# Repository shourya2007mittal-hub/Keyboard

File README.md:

# KEYBOARD
So I am making an 60% layout keyboard with 2 rotor encoders .So In total there will be 61 Keys and 2 rotor encoders for volume and britness controle but there aren't that many gpios in any devboard therefore I would be using keyboard matrix and diodes to restrict gosting and I choosed Raspberry Pico as controller because it supports KMK and have enought Gpios as well.I also added stabalizers for any keys whose size is over 1.75U
## Features

- Base on Raspberry pico
- Has 61 keys ( 60% Keyboard Matrix)
- Has 2 Rotor Encoder
  ### Schematic
  br>

  ###  PCB Design
<br>

### 3D Design

- ## Bill of Materials (BOM)

| # | Item | Description | Quantity | Unit Price (USD) | Total (USD) | Link |
|---|------|-------------|----------|------------------|-------------|------|
| 1 | 80Retros x HMX Volume | Mechanical switches (pack of 35) | 2 packs | 17.8 | 35.6 | https://stackskb.com/store/hmx-volume-0-pack-of-35/ |
| 2 | 1N4148 Diode | DO-35 switching diode | 61 | 0 | 0 | | Already have
| 3 | Raspberry Pi Pico H | RP2040 microcontroller board | 1 | 5.5 | 5.5 | https://robu.in/product/raspberry-pi-pico-with-headers/ |
| 4 |  Keycap Set | Full keycap set | 1 | 26.2 | 26.2 | https://stackskb.com/store/blue-and-blue-double-shot-abs-cherry-profile-keycaps-pre-order/
| 5 | Screw-In Stabilizers V2 | Keyboard stabilizers | 1 | 0 |0 | Already have |
| 6 | PCB  + Shipping | PCB fabrication (JLCPCB) | 1 |31.55| 31.55 | https://jlcpcb.com |

**Estimated Total Hardware Cost:** **USD 98.85**

## Hardware
- Raspberry Pico 
- Cherry MX compatible Switches
- Diode
- 2 layer PCB
- 2 Rotor Encoder

## Firmware
- It is Based on KMK and Circuit Python

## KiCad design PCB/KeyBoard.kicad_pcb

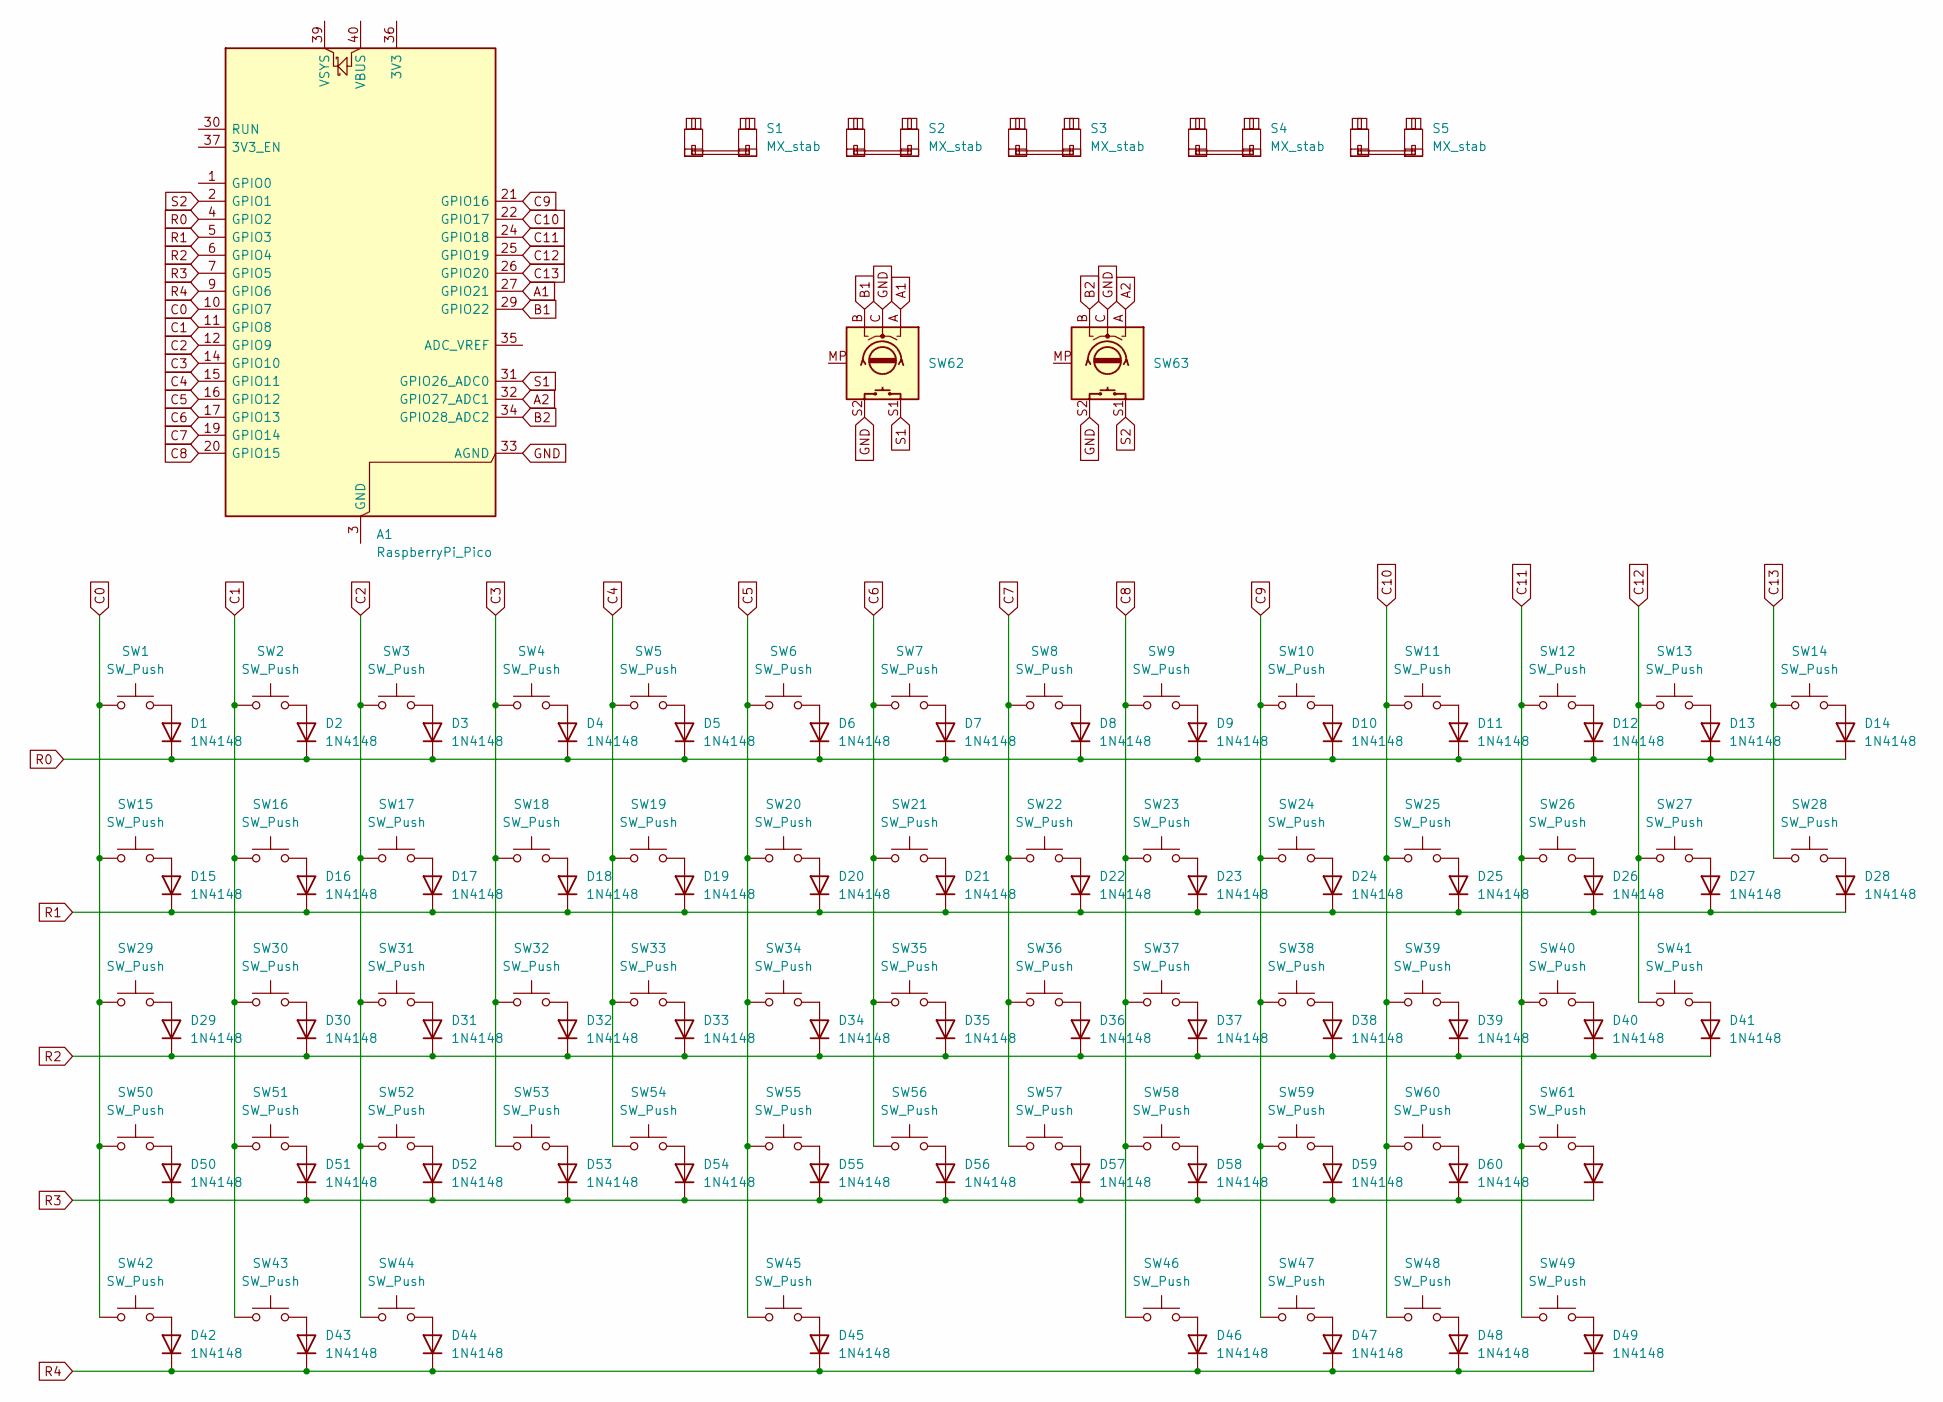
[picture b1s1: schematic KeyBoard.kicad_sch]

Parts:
A1: RaspberryPi_Pico; RaspberryPi_Pico_Common_Unspecified
D1, D2, D3, D4, D5, D6, D7, D8, D9, D10, D11, D12, D13, D14, D15, D16, D17, D18, D19, D20, D21, D22, D23, D24, D25, D26, D27, D28, D29, D30, D31, D32, D33, D34, D35, D36, D37, D38, D39, D40, D41, D42, D43, D44, D45, D46, D47, D48, D49, D50, D51, D52, D53, D54, D55, D56, D57, D58, D59, D60, D61: 1N4148; D_DO-35_SOD27_P7.62mm_Horizontal
S1: MX_stab; STAB_MX_2u
S2, S3: MX_stab; STAB_MX_2.25u
S4: MX_stab; STAB_MX_2.75u
S5: MX_stab; STAB_MX_6.25u
SW1, SW2, SW3, SW4, SW5, SW6, SW7, SW8, SW9, SW10, SW11, SW12, SW13, SW16, SW17, SW18, SW19, SW20, SW21, SW22, SW23, SW24, SW25, SW26, SW27, SW30, SW31, SW32, SW33, SW34, SW35, SW36, SW37, SW38, SW39, SW40, SW51, SW52, SW53, SW54, SW55, SW56, SW57, SW58, SW59, SW60: SW_Push; SW_Cherry_MX_1.00u_PCB
SW14: SW_Push; SW_Cherry_MX_2.00u_PCB
SW15: SW_Push; SW_Cherry_MX_1.50u_PCB
SW28: SW_Push; SW_Cherry_MX_1.50u_Plate
SW29: SW_Push; SW_Cherry_MX_1.75u_PCB
SW41, SW50: SW_Push; SW_Cherry_MX_2.25u_PCB
SW42, SW43, SW44, SW46, SW48, SW49: SW_Push; SW_Cherry_MX_1.25u_PCB
SW45: SW_Push; SW_Cherry_MX_6.25u_PCB
SW47: SW_Push; SW_Cherry_MX_1.25u_Plate
SW61: SW_Push; SW_Cherry_MX_2.75u_PCB
SW62, SW63: RotaryEncoder_Switch_MP; RotaryEncoder_Alps_EC11E-Switch_Vertical_H20mm

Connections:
A1: A1.27 (GPIO21), SW62.A
A2: A1.32 (GPIO27_ADC1), SW63.A
B1: A1.29 (GPIO22), SW62.B
B2: A1.34 (GPIO28_ADC2), SW63.B
C0: A1.10 (GPIO7), SW1.1, SW15.1, SW29.1, SW42.1, SW50.1
C1: A1.11 (GPIO8), SW2.1, SW16.1, SW30.1, SW43.1, SW51.1
C2: A1.12 (GPIO9), SW3.1, SW17.1, SW31.1, SW44.1, SW52.1
C3: A1.14 (GPIO10), SW4.1, SW18.1, SW32.1, SW53.1
C4: A1.15 (GPIO11), SW5.1, SW19.1, SW33.1, SW54.1
C5: A1.16 (GPIO12), SW6.1, SW20.1, SW34.1, SW45.1, SW55.1
C6: A1.17 (GPIO13), SW7.1, SW21.1, SW35.1, SW56.1
C7: A1.19 (GPIO14), SW8.1, SW22.1, SW36.1, SW57.1
C8: A1.20 (GPIO15), SW9.1, SW23.1, SW37.1, SW46.1, SW58.1
C9: A1.21 (GPIO16), SW10.1, SW24.1, SW38.1, SW47.1, SW59.1
C10: A1.22 (GPIO17), SW11.1, SW25.1, SW39.1, SW48.1, SW60.1
C11: A1.24 (GPIO18), SW12.1, SW26.1, SW40.1, SW49.1, SW61.1
C12: A1.25 (GPIO19), SW13.1, SW27.1, SW41.1
C13: A1.26 (GPIO20), SW14.1, SW28.1
GND: A1.33 (AGND), SW62.C, SW62.S2, SW63.C, SW63.S2
unnamed: A1.3 (GND), A1.8 (GND), A1.13 (GND), A1.18 (GND), A1.23 (GND), A1.28 (GND), A1.38 (GND)
unnamed: D1.2 (A), SW1.2
unnamed: D2.2 (A), SW2.2
unnamed: D3.2 (A), SW3.2
unnamed: D4.2 (A), SW4.2
unnamed: D5.2 (A), SW5.2
unnamed: D6.2 (A), SW6.2
unnamed: D7.2 (A), SW7.2
unnamed: D8.2 (A), SW8.2
unnamed: D9.2 (A), SW9.2
unnamed: D10.2 (A), SW10.2
unnamed: D11.2 (A), SW11.2
unnamed: D12.2 (A), SW12.2
unnamed: D13.2 (A), SW13.2
unnamed: D14.2 (A), SW14.2
unnamed: D15.2 (A), SW15.2
unnamed: D16.2 (A), SW16.2
unnamed: D17.2 (A), SW17.2
unnamed: D18.2 (A), SW18.2
unnamed: D19.2 (A), SW19.2
unnamed: D20.2 (A), SW20.2
unnamed: D21.2 (A), SW21.2
unnamed: D22.2 (A), SW22.2
unnamed: D23.2 (A), SW23.2
unnamed: D24.2 (A), SW24.2
unnamed: D25.2 (A), SW25.2
unnamed: D26.2 (A), SW26.2
unnamed: D27.2 (A), SW27.2
unnamed: D28.2 (A), SW28.2
unnamed: D29.2 (A), SW29.2
unnamed: D30.2 (A), SW30.2
unnamed: D31.2 (A), SW31.2
unnamed: D32.2 (A), SW32.2
unnamed: D33.2 (A), SW33.2
unnamed: D34.2 (A), SW34.2
unnamed: D35.2 (A), SW35.2
unnamed: D36.2 (A), SW36.2
unnamed: D37.2 (A), SW37.2
unnamed: D38.2 (A), SW38.2
unnamed: D39.2 (A), SW39.2
unnamed: D40.2 (A), SW40.2
unnamed: D41.2 (A), SW41.2
unnamed: D42.2 (A), SW42.2
unnamed: D43.2 (A), SW43.2
unnamed: D44.2 (A), SW44.2
unnamed: D45.2 (A), SW45.2
unnamed: D46.2 (A), SW46.2
unnamed: D47.2 (A), SW47.2
unnamed: D48.2 (A), SW48.2
unnamed: D49.2 (A), SW49.2
unnamed: D50.2 (A), SW50.2
unnamed: D51.2 (A), SW51.2
unnamed: D52.2 (A), SW52.2
unnamed: D53.2 (A), SW53.2
unnamed: D54.2 (A), SW54.2
unnamed: D55.2 (A), SW55.2
unnamed: D56.2 (A), SW56.2
unnamed: D57.2 (A), SW57.2
unnamed: D58.2 (A), SW58.2
unnamed: D59.2 (A), SW59.2
unnamed: D60.2 (A), SW60.2
unnamed: D61.2 (A), SW61.2
R0: A1.4 (GPIO2), D1.1 (K), D2.1 (K), D3.1 (K), D4.1 (K), D5.1 (K), D6.1 (K), D7.1 (K), D8.1 (K), D9.1 (K), D10.1 (K), D11.1 (K), D12.1 (K), D13.1 (K), D14.1 (K)
R1: A1.5 (GPIO3), D15.1 (K), D16.1 (K), D17.1 (K), D18.1 (K), D19.1 (K), D20.1 (K), D21.1 (K), D22.1 (K), D23.1 (K), D24.1 (K), D25.1 (K), D26.1 (K), D27.1 (K), D28.1 (K)
R2: A1.6 (GPIO4), D29.1 (K), D30.1 (K), D31.1 (K), D32.1 (K), D33.1 (K), D34.1 (K), D35.1 (K), D36.1 (K), D37.1 (K), D38.1 (K), D39.1 (K), D40.1 (K), D41.1 (K)
R3: A1.7 (GPIO5), D50.1 (K), D51.1 (K), D52.1 (K), D53.1 (K), D54.1 (K), D55.1 (K), D56.1 (K), D57.1 (K), D58.1 (K), D59.1 (K), D60.1 (K), D61.1 (K)
R4: A1.9 (GPIO6), D42.1 (K), D43.1 (K), D44.1 (K), D45.1 (K), D46.1 (K), D47.1 (K), D48.1 (K), D49.1 (K)
S1: A1.31 (GPIO26_ADC0), SW62.S1
S2: A1.2 (GPIO1), SW63.S1

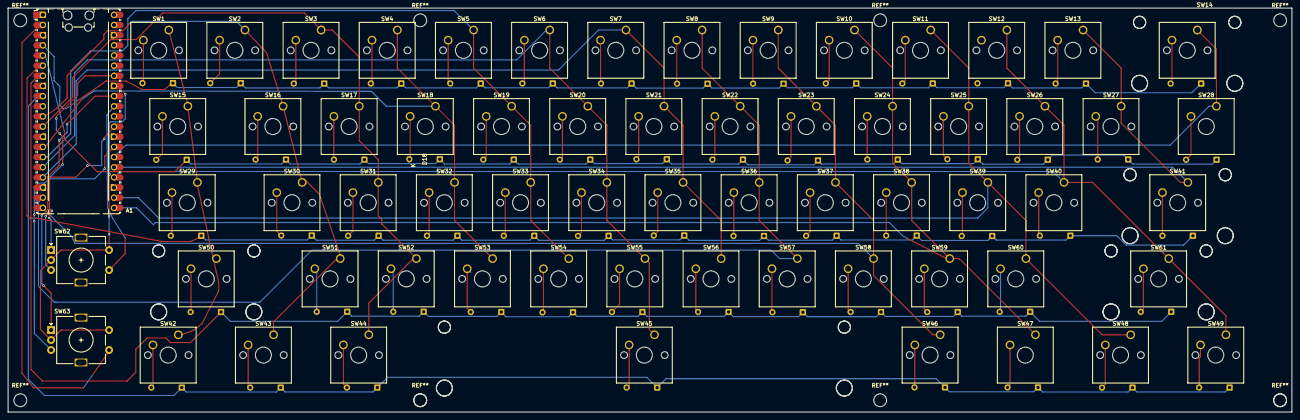
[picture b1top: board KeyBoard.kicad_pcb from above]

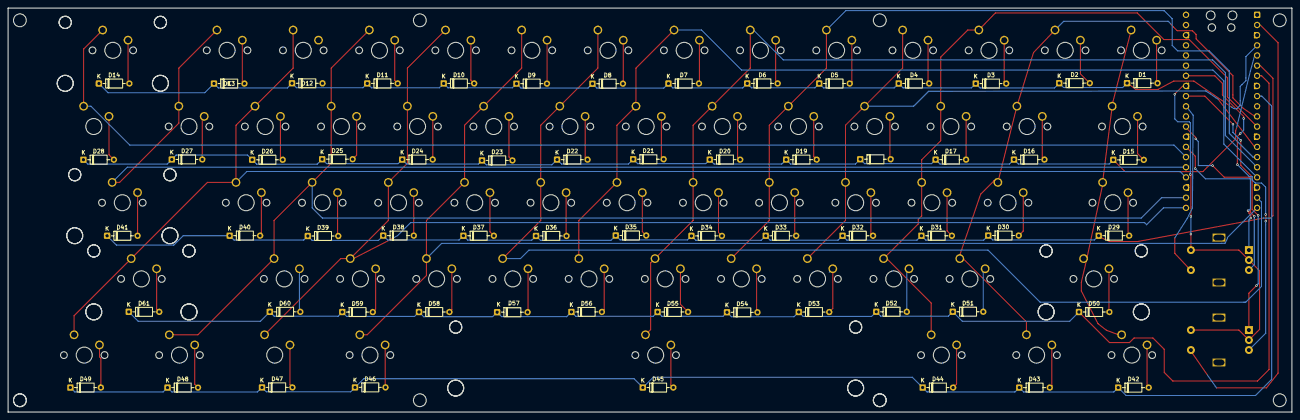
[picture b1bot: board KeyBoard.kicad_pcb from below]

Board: 2 copper layers, 321.0 x 101.0 mm, 130 parts (61 on the bottom side), 88 nets.
